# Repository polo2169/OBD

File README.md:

# Diagbox++ / OpenDiag PSA + Fiat + Renault

Socle open source pour construire un outil de diagnostic PSA/Stellantis avancé sans
réimplémenter les couches standard déjà disponibles.

Références principales :

- [arduino-psa-diag](https://github.com/ludwig-v/arduino-psa-diag) pour la recherche PSA UDS/KWP et les familles de calculateurs ;
- [PSA-RE](https://github.com/prototux/PSA-RE) pour les architectures AEE2004/AEE2010 et les descriptions DBMUXE ;
- [python-can](https://github.com/hardbyte/python-can) pour l'accès CAN ;
- [python-can-isotp](https://github.com/pylessard/python-can-isotp) pour ISO-TP ;
- [udsoncan](https://github.com/pylessard/python-udsoncan) pour UDS ISO 14229 ;
- [VanBus](https://github.com/0xCAFEDECAF/VanBus) pour les architectures PSA VAN ;
- [OBD-LCD-display-for-PSA](https://github.com/nico1080/OBD-LCD-display-for-PSA) et [AutoWP](https://autowp.github.io) comme sources complémentaires.
Starter kit open source pour construire un outil de diagnostic automobile modulaire :

- **ESP32 / ESP32-S3** : passerelle CAN/TWAI vers USB série ou Wi-Fi privé ;
- **RDK X5 ou PC Linux** : moteur de diagnostic, stockage, API et IA ;
- **React** : interface utilisateur ;
- **Base YAML PSA** : véhicules, calculateurs, DIDs et DTC documentés ;
- **Simulateur** : développement sans voiture.

lien interressant : https://driver.top/exp/695220
https://driver.top/exp/700838/
https://github.com/Barracuda09/PyPSADiag

https://driver.top/exp/253246/

## Organisation du dépôt

Le dépôt contient deux sous-projets séparés et une base véhicule commune :

```text
backend/ + frontend/ + firmware/esp32-gateway/   application de diagnostic OBD
openpilot/                                       laboratoire ADAS PSA T9
database/                                        données véhicule partagées
data/                                            captures et résultats locaux
```

La documentation du laboratoire caméra, Matek, simulation, MADS/RVV et harnais
est centralisée dans [openpilot/README.md](openpilot/README.md). Le contrat des
données partagées est décrit dans [database/README.md](database/README.md).

## État de cette version

Fonctions disponibles :

- écoute CAN passive sur l'ESP32 ;
Code : B1238- protocole USB/TCP v6 : contrôle JSON Lines et trames CAN compactes sans filtrage ;
- lecture et journalisation de trames ;
- transport virtuel pour les tests ;
- lecture OBD-II générique simulée ;
- pile ISO-TP complète via `python-can-isotp` (trames simples et segmentées) ;
- client UDS via `udsoncan` avec gestion des NRC et temporisations P2/P2* ;
- scanner UDS configurable avec session réutilisée par calculateur ;
- lecture et décodage des DIDs d'identification ISO 14229 ;
- lecture DID ciblée par API ;
- profil T9 enrichi avec 11 familles ECU sourcées et présence optionnelle explicite ;
- lecture UDS `0x19/0x02`, décodage des états et descriptions DTC PSA ;
- catalogue communautaire normalisé : 355 variantes et 40 840 définitions sourcées ;
- mode « capteurs uniquement » avec découverte des PID OBD-II Mode 01 supportés ;
- direct hybride Fiat/Peugeot : CAN constructeur passif prioritaire et complément
  OBD Mode 01 borné par profil (régime, vitesse, températures, admission et
  tension calculateur/batterie) ;
- arbitrage transactionnel du transport partagé : une capture peut rester active
  pendant le polling OBD sans mélanger les réponses ISO-TP avec un scan ECU ;
- catalogue multimarque de 29 services de maintenance, avec applicabilité par
  profil, équipement conditionnel, niveau de risque et verrouillage systématique
  des procédures non validées sur véhicule ;
- sessions JSONL détaillées : CAN, passerelle, ISO-TP, UDS/OBD, NRC et durées ;
- API FastAPI ;
- interface React ;
- navigation stabilisée autour de six modules : Garage, Diagnostic, Atelier,
  Learn, Database et Security & Workflow ;
- sélecteur de mode global Lecture seule / Maintenance contrôlée, avec
  préconditions, confirmation, retour immédiat au mode sûr et audit par VIN ;
- Live Data transversal avec ajout, modification et archivage de capteurs locaux
  au VIN, sans modifier la capture CAN d'origine ;
- garage multi-véhicules avec sélection persistante du VIN actif et chronologie
  consolidée des diagnostics, trajets et identifications ;
- replay temporel des captures CAN avec Peugeot vue du dessus, instruments, commandes et états ADAS ;
- reconstruction locale du mouvement par vitesse et angle du volant, avec cache de post-traitement sur le PC ;
- laboratoire OpenPilot compagnon séparé pour l'acquisition Matek/GoPro, les
  simulations T9 et la passerelle expérimentale MADS/RVV ;
- base PSA extensible avec niveaux de confiance ;
- séparation entre autorisation matérielle TX et filtrage applicatif lecture seule.
- mode « Diagnostic PSA avancé » : lecture de zones brutes, calcul seed/key hors
  ligne, clés candidates par ECU et actionneurs NAC strictement nommés ;
- profil firmware `esp32-tja1050-serial-psa-lab` à allowlist doublement vérifiée
  par le PC et l'ESP32, distinct du firmware de lecture seule.
- page « VIN & véhicule » : lecture UDS `22 F1 90` sur Peugeot, lecture OBD-II
  Mode 09 PID 02 sur Fiat, validation WMI et journalisation JSONL locale ;
- profil initial Fiat 500 en identification seule, avec les candidats Body Computer
  `7B0→7C0` et combiné `7B0→7C3` clairement marqués expérimentaux ;
- catalogue Fiat 500 enrichi en capteurs CAN passifs et PID EOBD, avec 9 533
  DTC génériques, 100 libellés Fiat et provenance détaillée dans
  [docs/FIAT_500_DIAGNOSTIC_SOURCES.md](docs/FIAT_500_DIAGNOSTIC_SOURCES.md) ;
- profil Renault Trafic III (X82) en profil diagnostic complet : 8 familles ECU
  sourcées depuis le catalogue communautaire ddt4all, scan UDS/DTC générique et
  lecture VIN OBD-II ; pas encore de décodeur CAN passif constructeur (à
  construire via le module Learn sur véhicule réel, voir
  `docs/ECU_CATALOG_RENAULT_TRAFIC.md`) ;
- profil Renault Trafic II (X83) séparé, limité aux lectures EOBD sûres sur le
  CAN 11 bits à 250 kbit/s (broches 6/14), avec avertissement explicite pour les
  variantes/calculatrices encore en K-Line ;
- sélection automatique du débit CAN 250/500 kbit/s par le profil véhicule avec
  confirmation du firmware avant toute lecture active ;
- sélection du véhicule actif générique par l'utilisateur (Garage, écran
  Véhicule & VIN) : chaque marque ajoutée au registre `database/<marque>/
  vehicles/*.yaml` apparaît automatiquement, sans code spécifique par marque.

## Architecture

Le contrat fonctionnel et les règles de sécurité sont décrits dans
[docs/ARCHITECTURE.md](docs/ARCHITECTURE.md).

```text
OBD-II
  │
Transceiver CAN automobile
  │
ESP32-S3
  │ Wi-Fi privé / TCP ou USB série (protocole v6)
  │
RDK X5 ou PC
  ├── FastAPI
  ├── udsoncan
  ├── python-can-isotp
  ├── Transports CAN / série / virtuel
  ├── Base PSA YAML
  ├── Historique
  ├── Analyse acoustique
  └── React
```

## Lancer toute l'application

### Première installation

Depuis la racine du dépôt, préparer une fois les dépendances du backend et du
frontend :

```bash
cd backend
python3 -m venv .venv
./.venv/bin/pip install -r requirements.txt
test -f .env || cp .env.example .env

cd ../frontend
npm install
cd ..
```

Le fichier `backend/.env` choisit le matériel utilisé. Pour travailler sans
voiture, conserver `TRANSPORT=virtual`. Pour la passerelle USB, utiliser
`TRANSPORT=esp32_serial` et renseigner son `SERIAL_PORT`.

Les réglages et observations propres à la machine sont écrits dans
`data/runtime/`, qui n'est pas versionné. Les fichiers `data/*.example.json`
documentent les formats attendus sans publier de port série, VIN ou défaut
observé.

### Vérification avant commit

Depuis la racine du dépôt :

```bash
./scripts/check_project.sh
```

Cette commande exécute les tests backend et OpenPilot, les barrières MADS/RVV
natives, le contrôle TypeScript strict et le build frontend dans un répertoire
temporaire. Si PlatformIO est installé, elle compile aussi les firmwares sûrs par
défaut. La CI reprend ces contrôles et compile chaque profil de référence.

### Frontend et backend en une commande

Toujours depuis la racine du dépôt :

```bash
./scripts/start_app.sh
```

Le script lance simultanément :

- l'interface React sur <http://127.0.0.1:5173> ;
- l'API FastAPI sur <http://127.0.0.1:8000> ;
- la documentation de l'API sur <http://127.0.0.1:8000/docs>.

Les journaux des deux services restent visibles dans le même terminal. Utiliser
`Ctrl+C` pour arrêter proprement le frontend et le backend ensemble.

Pour forcer le simulateur sans modifier `backend/.env` :

```bash
TRANSPORT=virtual ./scripts/start_app.sh
```

Les ports peuvent également être changés ponctuellement ; le lanceur transmet
automatiquement le nouveau port du backend au frontend :

```bash
BACKEND_PORT=8002 FRONTEND_PORT=5174 ./scripts/start_app.sh
```

### Démarrage manuel, service par service

#### Backend

```bash
cd backend
python -m venv .venv
source .venv/bin/activate
# Windows : .venv\Scripts\Activate.ps1
pip install -r requirements.txt
cp .env.example .env
uvicorn app.main:app --reload
```

Documentation :

```text
http://127.0.0.1:8000/docs
```

#### Frontend

```bash
cd frontend
npm install
npm run dev
```

Interface :

```text
http://localhost:5173
```

### Replay véhicule et trajectoire

Ouvrir **Replay véhicule** dans la barre latérale, puis choisir une session. Le
backend parcourt le JSONL en flux, échantillonne les signaux à 10 Hz et conserve
le résultat dans `data/sessions/<session>.replay.json`. La capture originale n'est
jamais modifiée.

Le replay anime la vitesse, le régime moteur, le volant, les pédales, les
clignotants, les feux et les signaux ADAS disponibles. L'option **Enregistrer le
trajet GPS**, active par défaut, utilise la géolocalisation du navigateur et écrit
chaque position dans le JSONL avec l'heure, la précision, l'altitude, le cap et la
vitesse disponibles. Le navigateur doit être ouvert sur `localhost` ou via HTTPS.
Un refus de permission n'interrompt jamais la capture CAN.

Avec au moins deux positions exploitables, le replay synchronise la trace GPS aux
échantillons CAN. Une position unique sert seulement d'ancrage à la reconstruction
vitesse/volant. Sans GPS, l'origine et l'orientation restent arbitraires et la
trajectoire ne doit pas être superposée à une route réelle. La trace brute est
exportable en GeoJSON depuis le replay.

API correspondante :

```text
GET /api/learn/replay/{session_id}
GET /api/learn/replay/{session_id}?force=true
GET /api/learn/replay/{session_id}/route.geojson
```

#### Laboratoire OpenPilot associé

Les outils caméra/GoPro, les acquisitions Matek et ESP32, les replays vidéo,
le simulateur de couple T9, le firmware MADS/RVV et le harnais OBD-C vivent
désormais dans le sous-projet autonome [`openpilot/`](openpilot/README.md).

Ils partagent avec l'application OBD la base déclarative [`database/`](database/README.md)
et les formats de capture sous `data/`, mais ne font plus partie du backend
FastAPI. Les commandes opérationnelles sont regroupées dans
[openpilot/COMMANDES.md](openpilot/COMMANDES.md).

### Garage, véhicule actif et historique

Ouvrir **Garage & historique** avant de travailler sur une voiture. Le véhicule
chargé est mémorisé côté PC par son VIN et devient le contexte commun du direct,
des diagnostics, des DTC et des replays. Le sélecteur présent dans l'en-tête
permet ensuite de changer rapidement de dossier.

Chaque nouvelle capture CAN reçoit automatiquement le VIN actif. Les anciennes
captures restent volontairement « sans VIN » jusqu'à leur classement depuis le
Garage : leur association utilise un petit fichier annexe
`data/sessions/<session>.vehicle.json` et ne réécrit jamais le JSONL brut.

La chronologie d'un véhicule regroupe :

- ses lectures d'identité ;
- ses diagnostics ECU/DTC et leurs comparaisons avant/après ;
- ses captures CAN et trajets GPS, ouvrables directement dans le replay.

Le changement de véhicule est bloqué pendant une capture afin d'éviter qu'une
session soit enregistrée sous le mauvais VIN.

### Simulation

Le backend utilise `TRANSPORT=virtual` par défaut.

```bash
curl http://127.0.0.1:8000/api/system/status
curl -X POST http://127.0.0.1:8000/api/diagnostic/scan
curl -X POST http://127.0.0.1:8000/api/sensors/snapshot
curl -X POST http://127.0.0.1:8000/api/diagnostic/ecus/engine/dids/0xF190
curl http://127.0.0.1:8000/api/database/vehicles
curl -X POST http://127.0.0.1:8000/api/diagnostic/identity \
  -H 'Content-Type: application/json' \
  -d '{"vehicle_profile":"fiat_500_generic"}'
curl http://127.0.0.1:8000/api/database/dids
curl http://127.0.0.1:8000/api/diagnostic/live
```

## Firmware ESP32 / ESP32-S3

Le firmware utilise PlatformIO et le pilote TWAI Arduino.

Pour l'ESP32 classique associé au transceiver Waveshare SN65HVD230, le profil
passif Wi-Fi est désormais le profil par défaut :

```bash
cd firmware/esp32-gateway
pio run -e esp32-waveshare-wifi-readonly
pio run -e esp32-waveshare-wifi-readonly -t upload
```

Il crée le point d'accès `OpenDiag-ESP32` et écoute en TCP sur
`192.168.4.1:35000`. Le mot de passe de développement est `opendiag-safe`.
Avant un usage régulier, copier `include/secrets.example.hpp` vers
`include/secrets.hpp` et remplacer ce mot de passe. Le fichier secret n'est pas
versionné.

```bash
cd firmware/esp32-gateway
# ESP32 classique : firmware passif par défaut
pio run -e esp32-readonly
pio run -e esp32-readonly -t upload
pio device monitor -b 921600
```

Le firmware actif doit être demandé explicitement. Il est nécessaire même pour une
lecture UDS/OBD, car une lecture implique d'émettre une requête CAN :

```bash
pio run -e esp32-active
pio run -e esp32-active -t upload
```

Pour le TJA1050 sur GPIO 5/4 et la liaison USB série, préférer le profil verrouillé
qui n'autorise dans le firmware que les lectures OBD/UDS documentées :

```bash
pio run -e esp32-tja1050-serial-diagnostic -t upload
```

Pour une carte ESP32-S3, utiliser respectivement `esp32-s3-readonly` et
`esp32-s3-active`. Vérifier le modèle avant le flash : un pont USB CP2102 ne suffit
pas à distinguer la famille de la puce.

Pour un diagnostic actif réel, il faut à la fois le firmware `active` et
`CAN_TX_ENABLED=true` dans le backend. `READ_ONLY=true` doit rester activé pour
bloquer les services UDS d'écriture, programmation, effacement et sécurité.

Voir [docs/ESP32_TEST.md](docs/ESP32_TEST.md) pour le premier essai sur véhicule.

### VIN et profil Fiat 500

La page **VIN & véhicule** propose la Peugeot 308 T9 et un premier profil Fiat
500. Pour la Peugeot, elle tente le DID UDS standard `F190` sur le BSI puis le
calculateur moteur avant le repli OBD-II. Pour la Fiat, elle commence par la
commande normalisée `09 02` sur `7E0→7E8`, puis seulement en cas d'échec tente
les paires communautaires Fiat en lecture `22 F1 90`.

Le résultat contient le VIN, le WMI, le constructeur détecté, la méthode qui a
répondu et les champs d'identité disponibles. Toute l'opération est enregistrée
dans `data/sessions/*.jsonl`. Le profil Fiat est limité à l'identification tant
que l'année, la motorisation et la génération exacte ne sont pas confirmées.
Voir [docs/VEHICLE_IDENTITY.md](docs/VEHICLE_IDENTITY.md).

### Carnet d’entretien mécanique

La page **Entretien** conserve un historique séparé pour chaque VIN du Garage.
Une intervention peut contenir la date, le kilométrage et sa provenance, le
garage, le numéro et le montant de facture, la main-d’œuvre, un compte rendu et
la liste détaillée des pièces montées. Chaque pièce accepte son fabricant, les
références et numéros de série retirés puis montés, sa quantité, son prix et sa
date de garantie.

Le kilométrage peut être prérempli directement depuis le signal CAN validé
quand la lecture OBD est active. Pour une intervention passée, le bouton
**Auto selon la date** recherche les relevés CAN, factures, interventions et
relevés d’huile qui encadrent la date. Une interpolation est toujours marquée
comme estimation (`≈`), conserve ses points de référence et reste modifiable.

Le bouton **Lire et préremplir la facture** extrait localement le texte d’un
PDF ou lance un OCR sur une photo. Il propose la date, le kilométrage, le garage,
le numéro et le total de facture ainsi que les références et numéros de série
clairement libellés. Le résultat reste un brouillon : tous les champs sont
éditables et rien n’est enregistré avant validation. La lecture PDF utilise
Poppler (`pdftotext`/`pdftoppm`) et l’OCR Tesseract (`fra+eng`) lorsqu’ils sont
disponibles ; aucun document n’est envoyé vers un service externe.

Les factures et justificatifs PDF/JPEG/PNG/WebP sont limités à 20 Mo chacun,
renommés avec un identifiant interne et accompagnés d’une empreinte SHA-256. Ils
sont stockés avec le dossier du véhicule sous
`data/diagnostics/<constructeur>/<VIN>/maintenance/`. Une modification crée une
révision d’archive avant de remplacer la fiche courante. Les interventions
apparaissent aussi dans la chronologie consolidée du Garage.

### Diagnostic PSA avancé

La page **Diagnostic PSA avancé** permet de lire n'importe quel DID `0x22` sur
une paire ECU documentée et de calculer une réponse seed/key hors ligne. Ces
fonctions n'exposent aucun champ d'émission CAN arbitraire.

Les tests NAC documentés (écran et caméra) utilisent un profil dédié :

```bash
cd firmware/esp32-gateway
pio run -e esp32-tja1050-serial-psa-lab
pio run -e esp32-tja1050-serial-psa-lab -t upload
```

Ils restent verrouillés tant que `READ_ONLY=false`, `CAN_TX_ENABLED=true` et
`PSA_ACTUATOR_ENABLED=true` ne sont pas explicitement réunis. Le déverrouillage
de configuration possède son propre verrou `PSA_SECURITY_ACCESS_ENABLED=true`.
Chaque opération exige en plus les confirmations atelier dans l'interface.

Chaque page calculateur PSA contient également un atelier de télécodage issu du
catalogue PyPSADiag. Il impose une variante ECU exacte et le parcours
`lecture → sauvegarde VIN → diff → relecture anti-concurrence → écriture unique
→ contrôle`. Les écritures restent désactivées tant que
`PSA_TELECODING_WRITE_ENABLED=true` et `PSA_SECURITY_ACCESS_ENABLED=true` ne
sont pas réunis avec le mode Maintenance contrôlée et le firmware
`psa_lab_bounded_writes`. Les sauvegardes et rapports restent locaux dans
`data/runtime/telecoding/`.

Les commandes BSI de clignotants ne sont pas connues : elles apparaissent dans
le catalogue mais restent non exécutables. Voir [docs/PSA_ADVANCED.md](docs/PSA_ADVANCED.md).

### Câblage prototype

Ne connecte jamais directement les GPIO de l'ESP32 à CAN-H/CAN-L.

```text
ESP32 GPIO TX/RX
       │
Transceiver CAN 3,3 V
       │
CAN-H / CAN-L
       │
OBD-II broches 6 et 14
```

Pour les premiers essais :

- alimentation ESP32 par batterie USB, câble du PC physiquement débranché ;
- masse commune ;
- véhicule immobile ;
- firmware en mode passif ;
- aucune résistance de terminaison supplémentaire sur une voiture déjà terminée.

### Waveshare SN65HVD230 3,3 V — montage retenu

L'ESP32 possède déjà le contrôleur TWAI : le MCP2515 n'est pas utilisé dans ce
montage. Le module Waveshare n'est pas isolé galvaniquement. Sa protection ESD ne
doit pas être confondue avec une isolation du PC.

| Waveshare | ESP32 / OBD | Remarque |
|---|---:|---|
| 3.3V | ESP32 3V3 | jamais OBD 16 |
| GND | ESP32 GND et OBD 5 | masse commune nécessaire |
| CAN_TX / D | GPIO 17 | de préférence via cavalier amovible |
| CAN_RX / R | GPIO 16 | logique 3,3 V |
| CANH | OBD 6 | câble court |
| CANL | OBD 14 | câble court |

Le schéma de cette carte contient une résistance `R2` de 120 ohms entre CAN-H et
CAN-L. Elle doit être dessoudée pour une connexion en dérivation sur la prise OBD,
le réseau du véhicule étant déjà terminé. Le premier essai se fait avec le profil
`esp32-waveshare-wifi-readonly`, la liaison TX idéalement ouverte, une batterie USB
et aucun câble entre l'ESP32 et le PC.

Le PC se connecte ensuite au réseau Wi-Fi de l'ESP32 et enregistre directement les
captures dans `data/sessions`. La file RAM du firmware absorbe les variations
courtes ; les compteurs `wifi_dropped_messages` et les numéros `seq` rendent toute
perte visible. Sans carte SD, une coupure Wi-Fi prolongée ne peut pas être récupérée.

Le module TJA1050 câblé selon le tutoriel ESP32 (`TX=GPIO5`, `RX=GPIO4`) dispose
des profils Wi-Fi équivalents `esp32-tja1050-wifi-readonly` et
`esp32-tja1050-wifi-active`. Utiliser le premier pour toute validation initiale.

### Module MCP2515 + TJA1050

Le MCP2515 est pris en charge avec la bibliothèque maintenue
[`autowp-mcp2515`](https://github.com/autowp/arduino-mcp2515), épinglée en version
1.3.1. Les profils disponibles sont :

```text
esp32-mcp2515-8mhz-readonly
esp32-mcp2515-8mhz-active
esp32-mcp2515-16mhz-readonly
esp32-mcp2515-16mhz-active
esp32-dual-can-16mhz-serial-diagnostic
esp32-dual-can-16mhz-serial-psa-lab
```

Choisir la fréquence inscrite sur le quartz métallique du module (`8.000` ou
`16.000`). Le profil `readonly` place matériellement le MCP2515 en mode
`listen-only`.

Le TJA1050 est un composant 5 V. Un module MCP2515/TJA1050 alimenté en 5 V ne doit
pas être relié directement aux GPIO 3,3 V de l'ESP32 : utiliser un traducteur de
niveaux logique adapté au SPI. Le câblage logique prévu, de part et d'autre de ce
traducteur, est :

| MCP2515 | ESP32 | Direction |
|---|---:|---|
| SCK | GPIO 18 | ESP32 vers MCP2515 |
| SO / MISO | GPIO 19 | MCP2515 vers ESP32 |
| SI / MOSI | GPIO 23 | ESP32 vers MCP2515 |
| CS | GPIO 5 en MCP seul, GPIO 27 en double CAN | ESP32 vers MCP2515 |
| INT | non connecté en MCP seul, GPIO 26 en double CAN | MCP2515 vers ESP32 |
| GND | GND | masse commune |

Alimenter le module en 5 V régulé depuis l'USB, jamais directement depuis le 12 V
de la broche 16 OBD. Vérifier hors tension la résistance entre CAN-H et CAN-L : si
le module présente environ 120 ohms, retirer/désactiver sa terminaison avant de le
brancher au véhicule, déjà terminé. CAN-H va sur OBD 6, CAN-L sur OBD 14 et la masse
commune sur OBD 4 ou 5.

Dans le montage double CAN de la Peugeot 308 T9, le tableau se lit avec
`CS=GPIO27` et `INT=GPIO26`. Le TJA/TWAI actuel reste sur OBD `6/14` ; le MCP2515
quartz `16.000` est relié à CAN-H OBD `3` et CAN-L OBD `8`. Le profil
`esp32-dual-can-16mhz-serial-diagnostic` lit les deux réseaux en même temps. Sur
`6/14`, il n'autorise que les requêtes OBD-II normalisées `01` et `09` adressées à
`0x7E0`, ainsi que le contrôle de flux ISO-TP nécessaire aux réponses. Sur `3/8`,
il conserve l'allowlist diagnostic en lecture seule. Le backend applique la même
séparation et la même double validation avant l'envoi, puis inscrit l'origine
`live`/`diagnostic` dans chaque capture.

Références électriques : [MCP2515 Microchip](https://www.microchip.com/content/dam/mchp/documents/APID/ProductDocuments/DataSheets/MCP2515-Family-Data-Sheet-DS20001801K.pdf),
[TJA1050 NXP](https://www.nxp.com/docs/en/data-sheet/TJA1050.pdf).

### Double CAN recommandé : deux ESP32 par UART

Le montage courant n'utilise plus le MCP2515. Une ESP32 principale écoute OBD
`6/14` avec TWAI et reste connectée au PC ; une seconde ESP32 utilise son TWAI sur
OBD `3/8`. Elles échangent les trames diagnostic à 2 Mbit/s :

| Principale | Satellite |
|---|---|
| GPIO17 TX | GPIO16 RX |
| GPIO16 RX | GPIO17 TX |
| GND | GND |

Flasher respectivement `esp32-dual-uart-main-diagnostic` et
`esp32-dual-uart-satellite-diagnostic`. Le backend continue à voir une seule
passerelle `dual_can` et sépare les trames `live` et `diagnostic`. La carte
principale n'accepte sur `6/14` que les lectures OBD-II `01`/`09` à destination de
`0x7E0` et leur contrôle de flux ISO-TP. Les requêtes UDS restent relayées
exclusivement vers le satellite `3/8`. Avec ce profil normal, effacement DTC,
écriture, routine et commande d'actionneur restent bloqués sur les deux réseaux.
Le profil séparé `esp32-dual-uart-satellite-psa-lab` est requis pour une séance de
maintenance ; même dans ce mode, seul `14 FFFFFF` et les rares actions PSA nommées
de l'allowlist firmware peuvent franchir la satellite.

### Transceiver TJA1050 seul

Un module portant des broches telles que `VCC`, `GND`, `CTX/TXD`, `CRX/RXD`,
`CANH` et `CANL` est un transceiver seul. C'est le montage le plus simple avec
l'ESP32, car il utilise directement le pilote TWAI et les profils `esp32-readonly`
ou `esp32-active` :

| TJA1050 | ESP32 / OBD | Remarque |
|---|---|---|
| VCC | 5 V USB régulé | jamais OBD 16 (12 V) |
| GND | GND ESP32 et OBD 4/5 | masse commune |
| CTX / TXD | GPIO 5 | liaison directe admise, VIH minimal TJA1050 = 2 V |
| CRX / RXD | GPIO 4 | adaptation 5 V vers 3,3 V obligatoire |
| CANH | OBD 6 | bus CAN High |
| CANL | OBD 14 | bus CAN Low |

Pour CRX/RXD, utiliser de préférence un traducteur de niveau rapide. À défaut, un
pont résistif 10 kohms entre RXD et GPIO 4, puis 18 kohms entre GPIO 4 et GND,
abaisse 5 V à environ 3,2 V. Vérifier au multimètre avant de raccorder GPIO 4.
Comme pour le MCP2515, retirer ou désactiver toute terminaison 120 ohms présente
sur le module avant raccordement au véhicule.

## Protocole passerelle

Les messages de contrôle restent en JSON Lines. Depuis le protocole 6, les trames
CAN utilisent sur le fil une ligne hexadécimale compacte afin de rester sous la
limite du pont CP2102 à 921 600 bauds, même sur un bus chargé :

```text
{"type":"hello","protocol":6,"device":"opendiag-esp32","firmware":"0.7.2-framed-diagnostic-lock","diagnostic_read_only":true,"bitrate":500000}
F,1E240,2A,7E8,20,0362F19000000000
{"type":"stats","rx":1200,"tx":0,"dropped":0,"bus_off":0,"rx_error_counter":0,"tx_error_counter":0}
```

Le backend développe immédiatement chaque ligne `F` et écrit toujours un JSONL
complet dans `data/sessions`, avec horodatages ESP/PC, identifiant, données et
événements de perte. Le fichier est vidé périodiquement puis synchronisé sur disque
à l'arrêt de la capture avant de lancer le post-traitement.

Commandes autorisées par défaut :

```json
{"type":"set_filter","ids":[2015,2024]}
{"type":"clear_filter"}
{"type":"ping"}
{"type":"get_status"}
```

La commande `can_tx` n'est disponible que dans un firmware actif ou dans le profil
`esp32-tja1050-serial-diagnostic`. Ce dernier verrouille aussi côté ESP les
identifiants et services autorisés en lecture. Le format étendu et les huit octets
maximum sont validés avant émission.

## Base PSA

Les fichiers de `database/psa` contiennent uniquement des éléments standards ou des exemples
marqués comme expérimentaux. Une donnée PSA ne doit être ajoutée qu'avec :

- une source ;
- un véhicule ou une architecture ;
- un niveau de confiance ;
- un niveau d'accès.

Le profil 308 T9 2018 contient maintenant moteur, boîte, ABS/ESP, BSI, airbag,
direction assistée, combiné, climatisation, caméra multifonction, aide au
stationnement et télématique. Les adresses proviennent d'un catalogue de familles :
les équipements optionnels ne sont considérés présents qu'après une réponse UDS.

Le catalogue DTC importé conserve sa provenance GPL-3.0 et la révision exacte. Une
description reste communautaire jusqu'à identification de la variante ECU ; le code
brut et l'octet d'état sont toujours conservés dans le rapport.

## Effacement des défauts

Le service UDS `0x14` est implémenté mais verrouillé par défaut. Il ne devient
accessible qu'avec `DTC_CLEAR_ENABLED=true`, `READ_ONLY=false`, `CAN_TX_ENABLED=true`,
une confirmation spécifique à l'ECU et quatre préconditions. ABS, airbag, BSI,
caméra et direction assistée demandent en plus `SAFETY_ECU_CLEAR_ENABLED=true`.
Le firmware doit annoncer `psa_lab=true`. Le workflow lit la mémoire du seul ECU
avant l'effacement, exige la réponse exacte `0x54`, puis relit immédiatement la
même mémoire et conserve les preuves avant/après dans la trace de session.

Effacer un DTC ne répare pas la panne et ne garantit pas la disparition d'un message
au tableau de bord : tout défaut encore présent sera recréé. Toujours sauvegarder le
rapport avant effacement puis relire immédiatement les DTC.

Les exports texte, CSV, candump ou JSONL de Diagbox peuvent être chargés depuis la
page **Diagnostic véhicule**. L'importeur reconstitue ISO-TP et classe les lectures
et services actifs hors véhicule ; une commande observée reste toujours marquée
non exécutable jusqu'à validation explicite.

Voir [docs/ECU_CATALOG.md](docs/ECU_CATALOG.md) pour les paires d'adresses, les sources
figées et la stratégie de détection.

## Tests

```bash
./scripts/check_project.sh
```

Pour ne lancer que le backend :

```bash
cd backend
./.venv/bin/pytest -p no:cacheprovider -q
```

La fixture globale force un transport virtuel et redirige toutes les données
d'exécution vers un répertoire temporaire. Les tests restent donc isolés du
fichier `.env`, du véhicule et des données locales.

## Important

Ce dépôt est un socle technique, pas un clone complet de l'outil constructeur.
Les adresses, DIDs et procédures spécifiques PSA doivent être acquises légalement,
documentées et testées sur banc avant utilisation.

La stratégie de réutilisation des projets existants et la feuille de route sont
décrites dans [docs/ARCHITECTURE.md](docs/ARCHITECTURE.md).

---

# V0.4 — pile de diagnostic standard

- remplacement du parseur ISO-TP minimal par `python-can-isotp` ;
- utilisation de `udsoncan` pour les requêtes, NRC et délais UDS ;
- réassemblage réel des réponses multi-trames ;
- inventaire des DIDs d'identification par ECU ;
- endpoint de lecture DID unitaire avec journalisation ;
- simulateur ECU ISO-TP multi-trame ;
- passerelle ESP32 active optionnelle et firmware passif par défaut ;
- garde-fous distincts `CAN_TX_ENABLED` et `READ_ONLY`.

---

# V0.5 — OpenDiag Learn : découverte comportementale

Le laboratoire peut maintenant chercher des correspondances sans connaître à
l'avance les identifiants PSA : il enregistre le bus en lecture seule, place des
marqueurs au moment d'une action, puis compare hors ligne les fenêtres avant et
après chaque marqueur répété.

## Enrichissement opendbc PSA

Le post-traitement charge également la base MIT
[`commaai/opendbc`](https://github.com/commaai/opendbc) :

- DBC `psa_aee2010_r3` figé à la révision
  `a0febba355168a5cb6168b535144c8c41a5ce323` ;
- 107 messages et 432 signaux disponibles ;
- décodage avec `cantools`, sans importer le code d'actionnement openpilot ;
- rapprochement automatique entre marqueurs et signaux DBC décodés ;
- inventaire CAN enrichi avec le nom du message et ses signaux connus ;
- provenance, licence et révision exposées dans l'interface et l'API.

Le port PSA amont documente la Peugeot 208 2019–2025, pas la 308 T9 2018.
Les noms opendbc restent donc marqués comme externes et non validés tant qu'une
capture répétée sur la 308 ne confirme pas leur comportement.
Le nom `r3` désigne ici la provenance du catalogue externe, pas l'architecture
attribuée à la voiture : les captures locales de `0x3F2` sont compatibles avec
la variante AEE2010 R2/EVO à commande de couple et CVM G2.

La copie amont et son attribution se trouvent dans
`database/psa/dbc/opendbc/`. Elle est utilisée uniquement sur les trames reçues :
activer `OPENDBC_ENABLED=true` ne permet aucune émission CAN.

Pour chaque identifiant CAN, le rapport calcule la fréquence, les DLC observés,
les octets variables, leur entropie et leurs basculements. Les candidats de type
fréquence, octet et bit sont classés avec un score, une confiance et une
justification. Le résultat est sauvegardé à côté de la capture :

```text
data/sessions/learn-<date>-<id>.jsonl
data/sessions/learn-<date>-<id>.correlations.json
```

## Workflow comportemental conseillé

1. Stabiliser le véhicule cinq secondes sans action.
2. Cliquer sur le marqueur `frein_appuye`.
3. Appuyer immédiatement sur le frein et maintenir l'action deux secondes.
4. Relâcher, stabiliser, puis répéter trois fois avec le même marqueur.
5. Arrêter et sauvegarder la capture.
6. Lancer l'analyse hors ligne depuis l'historique.
7. Refaire une seconde session pour confirmer les meilleurs candidats.

Un score élevé indique une corrélation temporelle, pas la signification certaine
du signal. Les feux stop, par exemple, peuvent faire varier simultanément la pédale,
le BSI et la consommation électrique.

## API de corrélation

```text
POST /api/learn/correlate/{session_id}
GET  /api/learn/correlations/{session_id}
GET  /api/learn/opendbc/catalog
```

Le corps facultatif du `POST` accepte `before_ms`, `after_ms`, `min_samples` et
`max_candidates_per_marker`.

---

# V0.3 — OpenDiag Learn

Cette version ajoute une chaîne de reverse engineering assisté, conçue pour analyser
des captures CAN obtenues légalement sur son propre véhicule ou sur un banc.

## Fonctions

- capture passive JSONL depuis ESP32, SocketCAN ou fichiers ;
- marqueurs utilisateur avant/après une opération ;
- import de captures ;
- regroupement des trames par identifiant ;
- détection heuristique de couples requête/réponse ;
- reconnaissance des services UDS courants ;
- calcul des différences entre deux fenêtres temporelles ;
- génération de propositions YAML ;
- validation humaine obligatoire ;
- aucune transmission CAN pendant l'analyse.

## Workflow

```text
1. Démarrer une capture passive.
2. Ajouter le marqueur "avant_lecture_abs".
3. Effectuer une lecture dans un outil autorisé.
4. Ajouter le marqueur "apres_lecture_abs".
5. Arrêter la capture.
6. Lancer l'analyse de la session.
7. Examiner les candidats.
8. Exporter une proposition YAML.
9. Valider manuellement avant ajout à la base.
```

## API Learn

```text
POST /api/learn/capture/start
POST /api/learn/capture/marker
POST /api/learn/capture/gps
POST /api/learn/capture/stop
GET  /api/learn/capture/status
GET  /api/learn/sessions
POST /api/learn/analyze/{session_id}
GET  /api/learn/proposals/{session_id}
POST /api/learn/export/{session_id}
POST /api/learn/correlate/{session_id}
GET  /api/learn/correlations/{session_id}
```

## Limites

L'analyse est heuristique. Une trame détectée comme UDS n'est pas nécessairement une
commande de diagnostic. Toute proposition reste marquée `experimental` jusqu'à
validation sur plusieurs véhicules ou sources fiables.

peux tu : séparer les historiques Peugeot/Fiat par VIN ;
générer et exporter un rapport diagnostic complet ;
ajouter les tests actionneurs confirmés ;
enrichir le catalogue de DIDs et DTC constructeur ;
éventuellement implémenter une passerelle compatible Diagbox — notre ESP32 n’est pas encore un émulateur de VCI Diagbox.

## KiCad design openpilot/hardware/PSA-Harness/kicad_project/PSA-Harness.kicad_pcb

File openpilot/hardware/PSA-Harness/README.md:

# Open Source All-in-One Harness / Harnessbox for PSA Cars (Peugeot, Citroen, Opel, Vauxhall, DS...)
The device is in development

If you have any questions contact me on Discord: elkoled

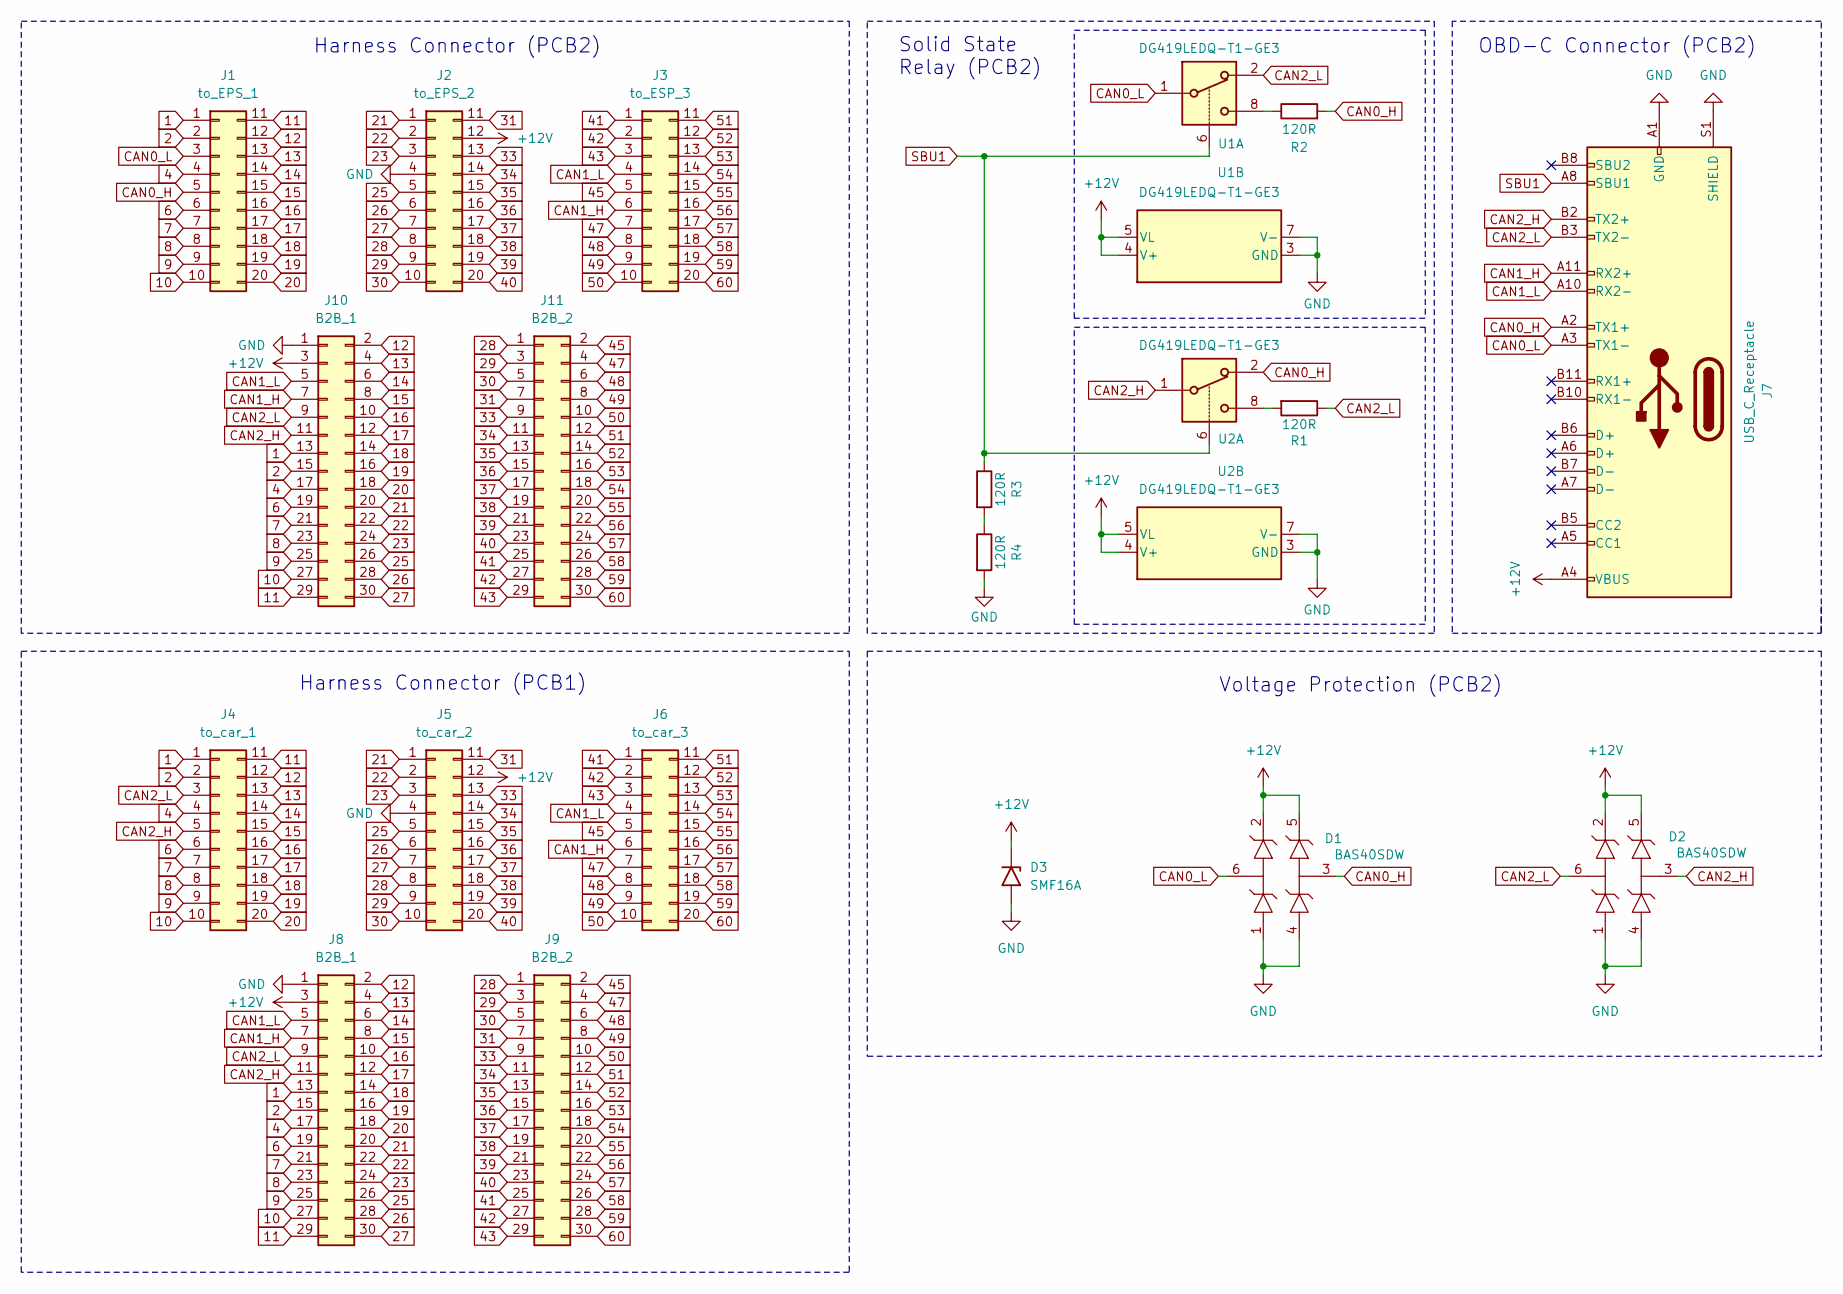
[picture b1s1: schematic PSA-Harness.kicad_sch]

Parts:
D1, D2: BAS40SDW; SOT-363_SC-70-6
D3: SMF16A; D_SOD-123
J1: to_EPS_1; Amphenol_10129381-920003BLF
J2: to_EPS_2; Amphenol_10129381-920003BLF
J3: to_ESP_3; Amphenol_10129381-920003BLF
J4: to_car_1; SAMTEC_ESW-110-44-F-D
J5: to_car_2; SAMTEC_ESW-110-44-F-D
J6: to_car_3; SAMTEC_ESW-110-44-F-D
J7: USB_C_Receptacle; GCT_USB4115-03-C_REVB4
J8, J10: B2B_1; SAMTEC_TW-10-03-T-T-320-100
J9, J11: B2B_2; SAMTEC_TW-10-03-T-T-320-100
R1, R2, R3, R4: 120R; R_1206_3216Metric
U1, U2: DG419LEDQ-T1-GE3; MSOP-8_3x3mm_P0.65mm

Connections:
1: J1.1, J4.1, J8.13, J10.13
2: J1.2, J4.2, J8.15, J10.15
4: J1.4, J4.4, J8.17, J10.17
6: J1.6, J4.6, J8.19, J10.19
7: J1.7, J4.7, J8.21, J10.21
8: J1.8, J4.8, J8.23, J10.23
9: J1.9, J4.9, J8.25, J10.25
10: J1.10, J4.10, J8.27, J10.27
11: J1.11, J4.11, J8.29, J10.29
12: J1.12, J4.12, J8.2, J10.2
13: J1.13, J4.13, J8.4, J10.4
14: J1.14, J4.14, J8.6, J10.6
15: J1.15, J4.15, J8.8, J10.8
16: J1.16, J4.16, J8.10, J10.10
17: J1.17, J4.17, J8.12, J10.12
18: J1.18, J4.18, J8.14, J10.14
19: J1.19, J4.19, J8.16, J10.16
20: J1.20, J4.20, J8.18, J10.18
21: J2.1, J5.1, J8.20, J10.20
22: J2.2, J5.2, J8.22, J10.22
23: J2.3, J5.3, J8.24, J10.24
25: J2.5, J5.5, J8.26, J10.26
26: J2.6, J5.6, J8.28, J10.28
27: J2.7, J5.7, J8.30, J10.30
28: J2.8, J5.8, J9.1, J11.1
29: J2.9, J5.9, J9.3, J11.3
30: J2.10, J5.10, J9.5, J11.5
31: J2.11, J5.11, J9.7, J11.7
33: J2.13, J5.13, J9.9, J11.9
34: J2.14, J5.14, J9.11, J11.11
35: J2.15, J5.15, J9.13, J11.13
36: J2.16, J5.16, J9.15, J11.15
37: J2.17, J5.17, J9.17, J11.17
38: J2.18, J5.18, J9.19, J11.19
39: J2.19, J5.19, J9.21, J11.21
40: J2.20, J5.20, J9.23, J11.23
41: J3.1, J6.1, J9.25, J11.25
42: J3.2, J6.2, J9.27, J11.27
43: J3.3, J6.3, J9.29, J11.29
45: J3.5, J6.5, J9.2, J11.2
47: J3.7, J6.7, J9.4, J11.4
48: J3.8, J6.8, J9.6, J11.6
49: J3.9, J6.9, J9.8, J11.8
50: J3.10, J6.10, J9.10, J11.10
51: J3.11, J6.11, J9.12, J11.12
52: J3.12, J6.12, J9.14, J11.14
53: J3.13, J6.13, J9.16, J11.16
54: J3.14, J6.14, J9.18, J11.18
55: J3.15, J6.15, J9.20, J11.20
56: J3.16, J6.16, J9.22, J11.22
57: J3.17, J6.17, J9.24, J11.24
58: J3.18, J6.18, J9.26, J11.26
59: J3.19, J6.19, J9.28, J11.28
60: J3.20, J6.20, J9.30, J11.30
+12V: D1.2, D1.5, D2.2, D2.5, D3.1 (A1), J2.12, J5.12, J7.A4 (VBUS), J7.A9 (VBUS), J7.B4 (VBUS), J7.B9 (VBUS), J8.3, J10.3, U1.4 (V+), U1.5 (VL), U2.4 (V+), U2.5 (VL)
CAN0_H: D1.3, J1.5, J7.A2 (TX1+), R2.2, U2.2
CAN0_L: D1.6, J1.3, J7.A3 (TX1-), U1.1
CAN1_H: J3.6, J6.6, J7.A11 (RX2+), J8.7, J10.7
CAN1_L: J3.4, J6.4, J7.A10 (RX2-), J8.5, J10.5
CAN2_H: D2.3, J4.5, J7.B2 (TX2+), J8.11, J10.11, U2.1
CAN2_L: D2.6, J4.3, J7.B3 (TX2-), J8.9, J10.9, R1.1, U1.2
GND: D1.1, D1.4, D2.1, D2.4, D3.2 (A2), J2.4, J5.4, J7.A1 (GND), J7.A12 (GND), J7.B1 (GND), J7.B12 (GND), J7.S1 (SHIELD), J8.1, J10.1, R4.2, U1.3 (GND), U1.7 (V-), U2.3 (GND), U2.7 (V-)
unnamed: R1.2, U2.8
unnamed: R2.1, U1.8
unnamed: R3.2, R4.1
SBU1: J7.A8 (SBU1), R3.1, U1.6, U2.6

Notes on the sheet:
Harness Connector (PCB2)
Voltage Protection (PCB2)
OBD-C Connector (PCB2)
Solid State Relay (PCB2)
Harness Connector (PCB1)

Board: 4 copper layers, 20 parts (9 on the bottom side), 66 nets, no tracks yet.

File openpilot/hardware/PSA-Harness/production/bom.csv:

Designator,Footprint,Quantity,Value,LCSC Part #
"D1, D2",SOT-363_SC-70-6,2,BAS40TW-AU,
D3,D_SOD-123,1,SMF16A,
J1,10129381-920003BLF,1,to_EPS_1,
"J10, J8",SAMTEC_TW-10-X-X-T-X-X,2,B2B_1,
"J11, J9",SAMTEC_TW-10-X-X-T-X-X,2,B2B_2,
J2,10129381-920003BLF,1,to_EPS_2,
J3,10129381-920003BLF,1,to_ESP_3,
J4,ESW-110-44-F-D,1,to_car_1,
J5,ESW-110-44-F-D,1,to_car_2,
J6,ESW-110-44-F-D,1,to_car_3,
J7,GCT_USB4115-03-C_REVB4,1,USB_C_Receptacle,
"R1, R2, R3, R4",1206,4,120R,
"U1, U2",MSOP-8_3x3mm_P0.65mm,2,DG419LEUA,

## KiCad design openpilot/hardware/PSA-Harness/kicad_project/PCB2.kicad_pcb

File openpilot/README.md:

# Openpilot — Peugeot 308 T9

Ce laboratoire contient le port expérimental de la Peugeot 308 II T9,
les outils d’acquisition et de rejeu, les tests et les sources du harnais PSA.
Il partage la base véhicule `database/` avec l’application de diagnostic OBD.

## Commencer ici

- [Comportement du code et limites](docs/ETAT_308_T9.md)
- [Protocole : direction dès 50 km/h, puis clignotant](docs/ESSAIS_308_T9.md)
- [Sources de l’overlay actif et construction](port/t9_lateral/README.md)
- [Collecte des journaux et export d’un dataset](docs/DATASET_308_T9.md)
- [Commandes caméra, GoPro, CAN passif et capteurs](COMMANDES.md)
- [Index technique](docs/README.md)

Le code conserve le plancher latéral de **67,1 km/h**, le RVV dès **40 km/h**
et la pause de direction au clignotant. Le pilotage dès 50 km/h et le changement
de voie après deux secondes restent des fonctions à étudier.

## Organisation

```text
openpilot/
├── port/t9_lateral/   overlay actif 308, tests et politique Panda
├── port/t9_shadow/    intégration en observation
├── tools/            acquisition, analyse, simulation et packaging
├── scripts/          collecte, construction, installation et vérification
├── tests/            tests du laboratoire hors véhicule
├── docs/             guides techniques et protocoles
├── parameters/       paramètres de simulation
├── examples/         exemples synthétiques
├── firmware/         passerelle PSA ESP32 et enregistreur GPS/IMU
└── hardware/         sources et production du harnais PSA OBD-C
```

Les comptes rendus, diagnostics, captures, vidéos, paquets compilés,
sauvegardes et sorties d’analyse restent locaux et sont exclus de Git.
Les sorties des outils utilisent `data/runtime/` ou `data/diagnostics/`.

Le dépôt comma/openpilot servant aux modèles et à la compilation est un dépôt
distinct, généralement `../openpilot`. Ce laboratoire distribue un overlay
contre une base précise.

## Vérifier le laboratoire

Depuis la racine OBD, avec l’environnement Python existant :

```sh
backend/.venv/bin/pip install -r openpilot/requirements.txt
cd openpilot
../backend/.venv/bin/pytest -p no:cacheprovider -q
```

La construction de l’overlay exige la base et les empreintes documentées dans
[son README](port/t9_lateral/README.md). La validation native sur cette base
est distincte des tests du laboratoire.

Le port actif reste expérimental. Les contrôles logiciels et USB ne constituent
pas une validation en conduite ; les essais physiques demandent un terrain fermé.
Le RVV agit sur la consigne Peugeot sans commande du frein de service.

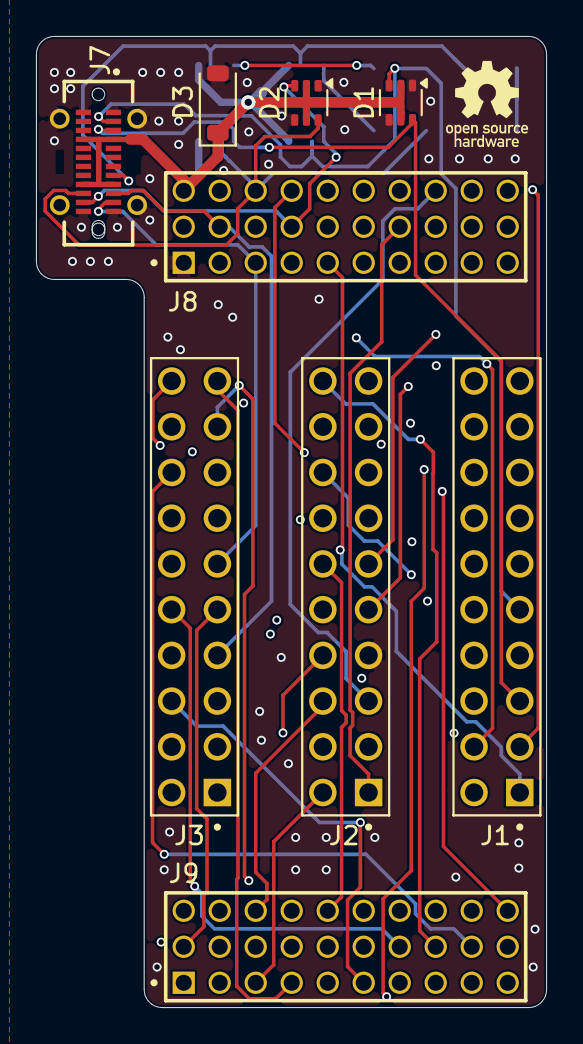
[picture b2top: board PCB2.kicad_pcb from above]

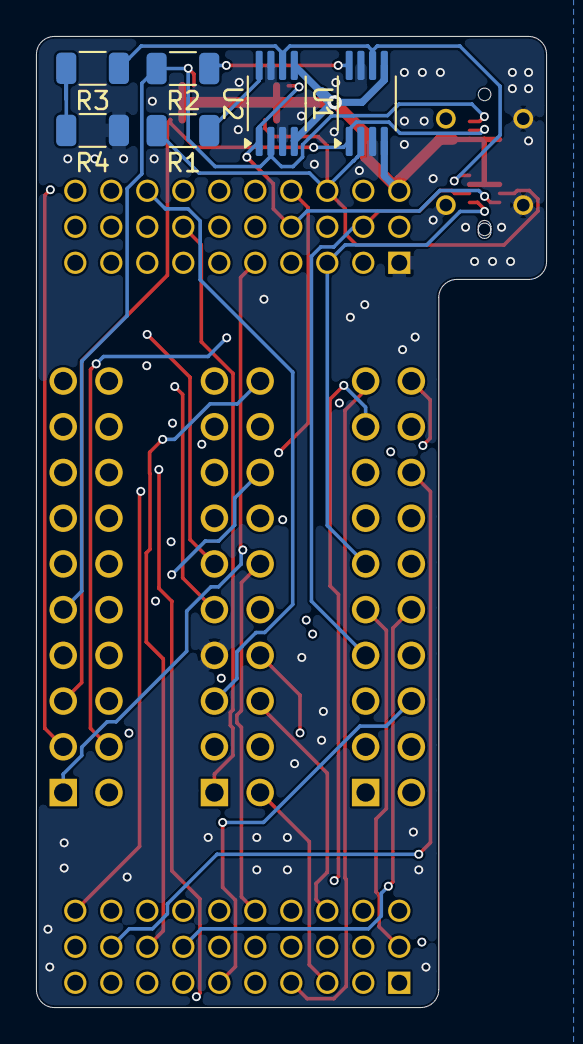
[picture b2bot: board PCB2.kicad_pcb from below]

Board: 4 copper layers, 28.3 x 54.0 mm, 15 parts (6 on the bottom side), 66 nets.

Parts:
D1, D2: BAS40TW-AU; SOT-363_SC-70-6
D3: SMF16A; D_SOD-123
J1: to_EPS_1; 10129381-920003BLF
J2: to_EPS_2; 10129381-920003BLF
J3: to_ESP_3; 10129381-920003BLF
J7: USB_C_Receptacle; GCT_USB4115-03-C_REVB4
J8: B2B_1; SAMTEC_TW-10-X-X-T-X-X
J9: B2B_2; SAMTEC_TW-10-X-X-T-X-X
R1, R2, R3, R4: 120R; R_1206_3216Metric
U1, U2: DG419LEUA; MSOP-8_3x3mm_P0.65mm

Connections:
1: J1.1, J8.13
2: J1.2, J8.15
4: J1.4, J8.17
6: J1.6, J8.19
7: J1.7, J8.21
8: J1.8, J8.23
9: J1.9, J8.25
10: J1.10, J8.27
11: J1.11, J8.29
12: J1.12, J8.2
13: J1.13, J8.4
14: J1.14, J8.6
15: J1.15, J8.8
16: J1.16, J8.10
17: J1.17, J8.12
18: J1.18, J8.14
19: J1.19, J8.16
20: J1.20, J8.18
21: J2.1, J8.20
22: J2.2, J8.22
23: J2.3, J8.24
25: J2.5, J8.26
26: J2.6, J8.28
27: J2.7, J8.30
28: J2.8, J9.1
29: J2.9, J9.3
30: J2.10, J9.5
31: J2.11, J9.7
33: J2.13, J9.9
34: J2.14, J9.11
35: J2.15, J9.13
36: J2.16, J9.15
37: J2.17, J9.17
38: J2.18, J9.19
39: J2.19, J9.21
40: J2.20, J9.23
41: J3.1, J9.25
42: J3.2, J9.27
43: J3.3, J9.29
45: J3.5, J9.2
47: J3.7, J9.4
48: J3.8, J9.6
49: J3.9, J9.8
50: J3.10, J9.10
51: J3.11, J9.12
52: J3.12, J9.14
53: J3.13, J9.16
54: J3.14, J9.18
55: J3.15, J9.20
56: J3.16, J9.22
57: J3.17, J9.24
58: J3.18, J9.26
59: J3.19, J9.28
60: J3.20, J9.30
+12V: D1.2, D1.5, D2.2, D2.5, D3.1 (A1), J2.12, J7.A4 (VBUS), J7.A9 (VBUS), J7.B4 (VBUS), J7.B9 (VBUS), J8.3, U1.4 (V+), U1.5 (VL), U2.4 (V+), U2.5 (VL)
CAN0_H: D1.3, J1.5, J7.A2 (TX1+), R2.2, U2.2
CAN0_L: D1.6, J1.3, J7.A3 (TX1-), U1.1
CAN1_H: J3.6, J7.A11 (RX2+), J8.7
CAN1_L: J3.4, J7.A10 (RX2-), J8.5
CAN2_H: D2.3, J7.B2 (TX2+), J8.11, U2.1
CAN2_L: D2.6, J7.B3 (TX2-), J8.9, R1.1, U1.2
GND: D1.1, D1.4, D2.1, D2.4, D3.2 (A2), J2.4, J7.A1 (GND), J7.A12 (GND), J7.B1 (GND), J7.B12 (GND), J7.S1 (SHIELD), J8.1, R4.2, U1.3 (GND), U1.7 (V-), U2.3 (GND), U2.7 (V-)
unnamed: R1.2, U2.8
unnamed: R2.1, U1.8
unnamed: R3.2, R4.1
SBU1: J7.A8 (SBU1), R3.1, U1.6, U2.6

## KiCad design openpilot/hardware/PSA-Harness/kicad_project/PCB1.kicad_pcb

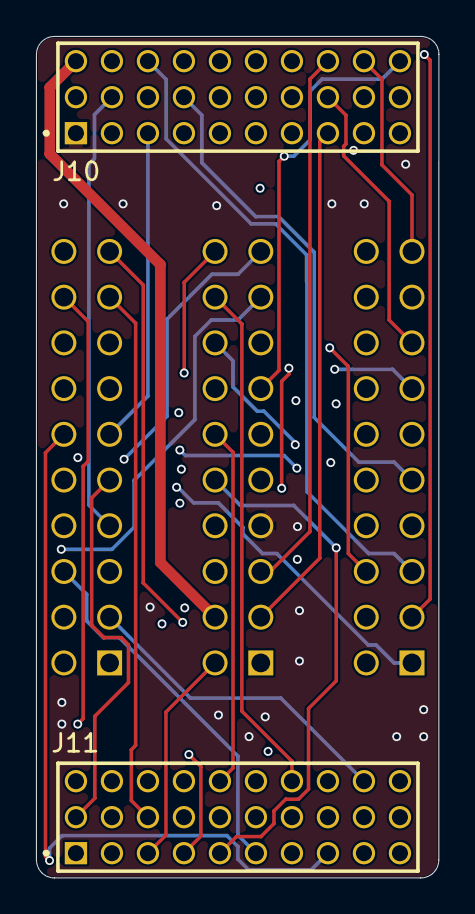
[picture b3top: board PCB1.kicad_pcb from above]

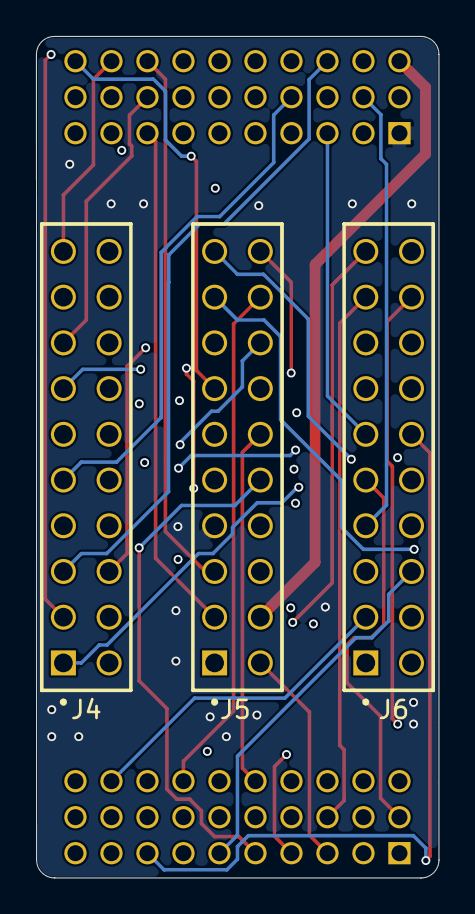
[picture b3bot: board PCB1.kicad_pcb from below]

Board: 4 copper layers, 22.4 x 46.8 mm, 5 parts (3 on the bottom side), 60 nets.

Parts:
J4: to_car_1; ESW-110-44-F-D
J5: to_car_2; ESW-110-44-F-D
J6: to_car_3; ESW-110-44-F-D
J10: B2B_1; SAMTEC_TW-10-X-X-T-X-X
J11: B2B_2; SAMTEC_TW-10-X-X-T-X-X

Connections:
1: J4.1, J10.13
2: J4.2, J10.15
4: J4.4, J10.17
6: J4.6, J10.19
7: J4.7, J10.21
8: J4.8, J10.23
9: J4.9, J10.25
10: J4.10, J10.27
11: J4.11, J10.29
12: J4.12, J10.2
13: J4.13, J10.4
14: J4.14, J10.6
15: J4.15, J10.8
16: J4.16, J10.10
17: J4.17, J10.12
18: J4.18, J10.14
19: J4.19, J10.16
20: J4.20, J10.18
21: J5.1, J10.20
22: J5.2, J10.22
23: J5.3, J10.24
25: J5.5, J10.26
26: J5.6, J10.28
27: J5.7, J10.30
28: J5.8, J11.1
29: J5.9, J11.3
30: J5.10, J11.5
31: J5.11, J11.7
33: J5.13, J11.9
34: J5.14, J11.11
35: J5.15, J11.13
36: J5.16, J11.15
37: J5.17, J11.17
38: J5.18, J11.19
39: J5.19, J11.21
40: J5.20, J11.23
41: J6.1, J11.25
42: J6.2, J11.27
43: J6.3, J11.29
45: J6.5, J11.2
47: J6.7, J11.4
48: J6.8, J11.6
49: J6.9, J11.8
50: J6.10, J11.10
51: J6.11, J11.12
52: J6.12, J11.14
53: J6.13, J11.16
54: J6.14, J11.18
55: J6.15, J11.20
56: J6.16, J11.22
57: J6.17, J11.24
58: J6.18, J11.26
59: J6.19, J11.28
60: J6.20, J11.30
+12V: J5.12, J10.3
CAN1_H: J6.6, J10.7
CAN1_L: J6.4, J10.5
CAN2_H: J4.5, J10.11
CAN2_L: J4.3, J10.9
GND: J5.4, J10.1
